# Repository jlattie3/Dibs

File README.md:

## Project Overview

Dibs is a full stack solution for helping students find open study spaces on campus. Light detection sensors send data that updates an iOS application to deliver clear visuals to open spots near them.
Dibs is a Spring 2020 ECE Senior Design project.

## Authors

- Jacob Lattie (iOS)
- Peter Nguyen (Server)
- Dylan Verstandig (BLE)
- Stephen Via (HW Sensor)
- Raish Wadhwaniya (HW Sensor)
- Dr. Lukas Graber (Advisor)

## Gallery

[Demonstration Video](https://www.youtube.com/watch?v=HJM3BfB4vtE)

## Hardware and Software

### Hardware

```
Raspberry Pi 3
nRF52840 Breakout
TLV2462 Op Amp
GL5528 LDR
```

### Software

```
Xcode 11.3.1
iOS 13+
Firebase Console
Adobe XD, Photoshop
```

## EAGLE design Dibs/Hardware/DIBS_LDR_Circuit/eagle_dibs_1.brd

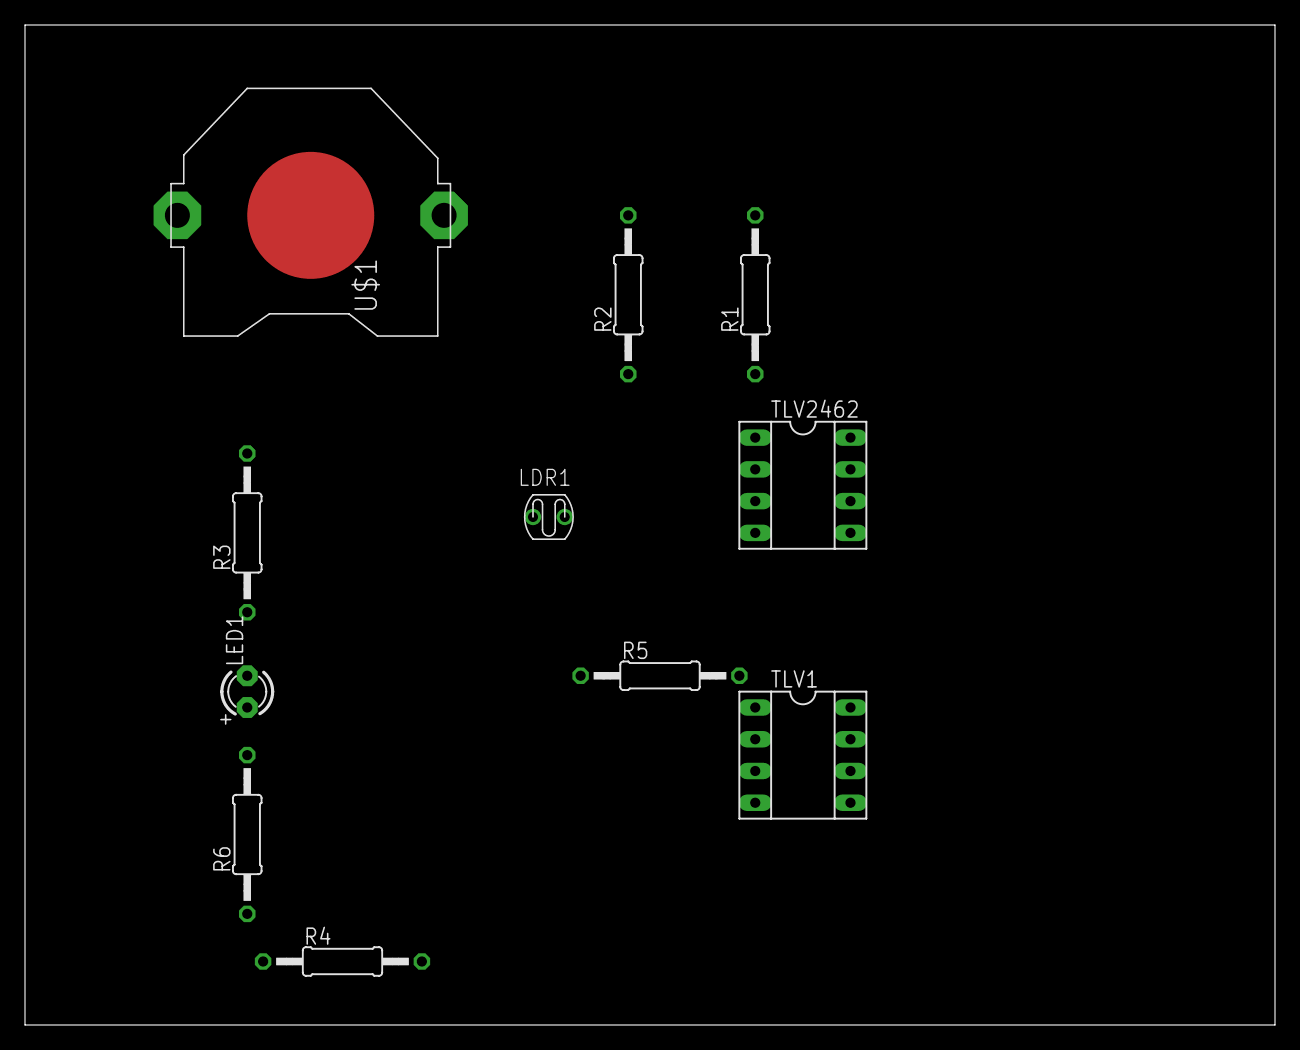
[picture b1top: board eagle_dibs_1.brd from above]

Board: 2 copper layers, 100.0 x 80.0 mm, 11 parts (0 on the bottom side), 8 nets, no tracks yet.

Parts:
LDR1: On: 555 Off: 855; LDR3MM
LED1: LED3MM
R1: 12.5K; 0207/12
R2: 753; 0207/12
R3: 9.166K; 0207/12
R4, R5: 1K; 0207/12
R6: 300; 0207/12
TLV1, TLV2462: Op amps; SOCKET-08
U$1: CR2032; CR2032-THRU

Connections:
GND: LDR1.P$2, LED1.K, R3.1, TLV1.3, TLV1.4, TLV2462.4, U$1.-
unnamed: LDR1.P$1, R1.1, TLV2462.3
unnamed: R2.1, R3.2, TLV2462.2
unnamed: R1.2, R2.2, TLV1.8, TLV2462.8, U$1.+1, U$1.+2
unnamed: LED1.A, R6.2
unnamed: R5.2, R6.1, TLV1.1
unnamed: R4.2, R5.1, TLV1.2
unnamed: R4.1, TLV2462.1

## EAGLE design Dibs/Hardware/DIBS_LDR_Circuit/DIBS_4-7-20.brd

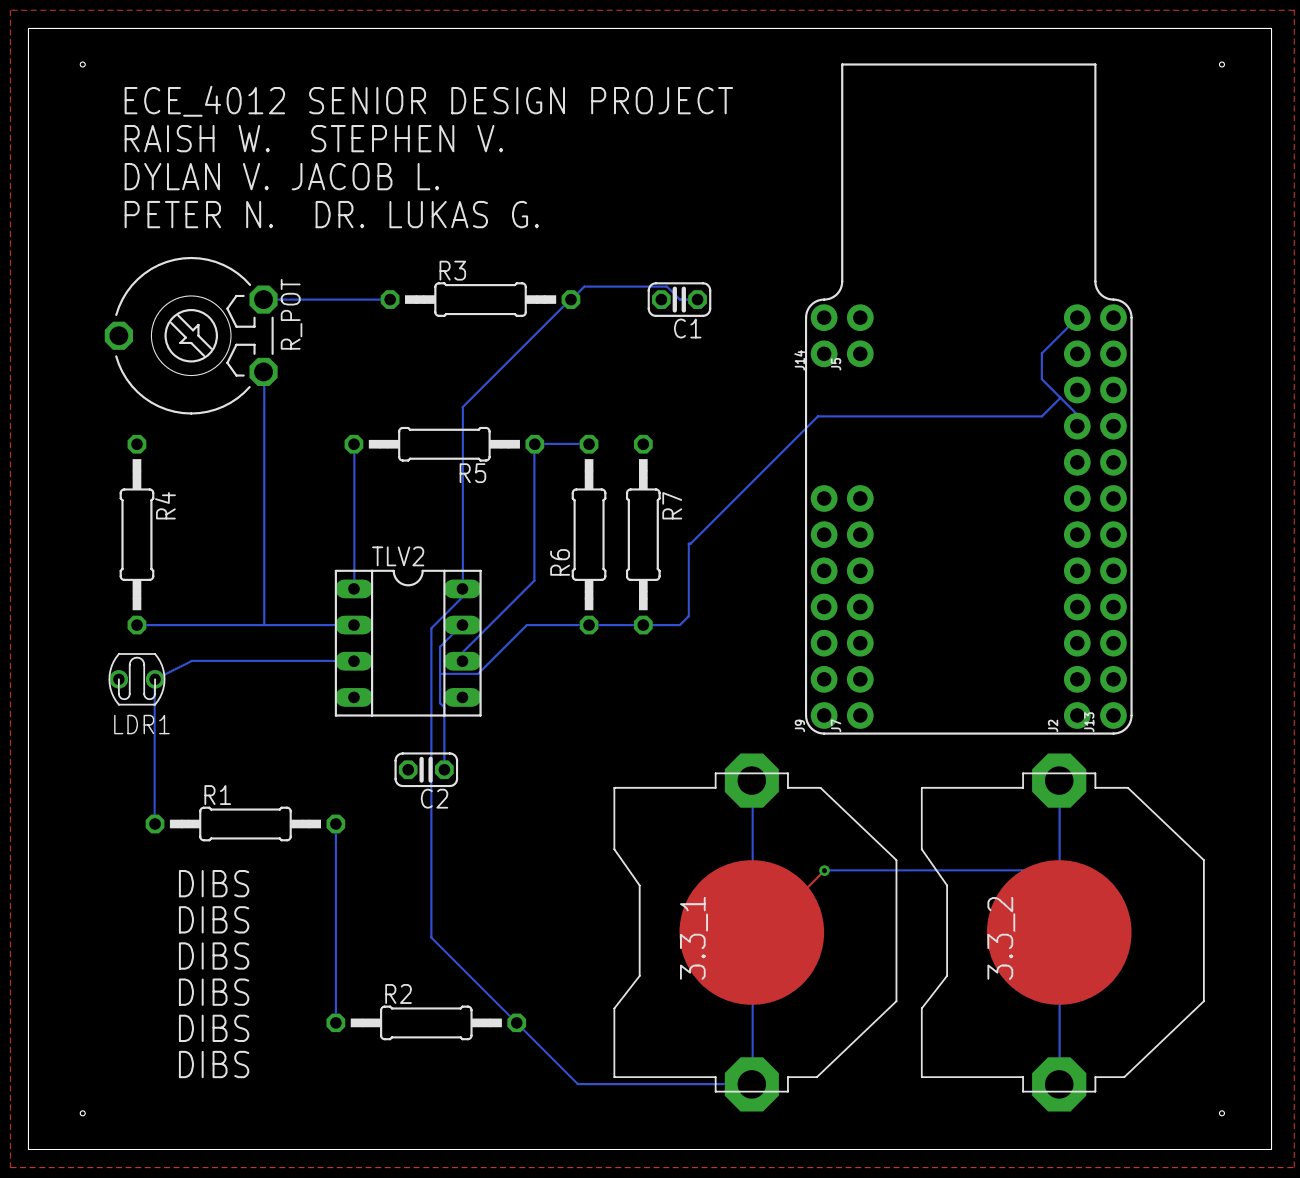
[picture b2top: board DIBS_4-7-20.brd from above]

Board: 2 copper layers, 87.3 x 78.7 mm, 20 parts (0 on the bottom side), 10 nets.

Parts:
3.3_1, 3.3_2: CR2032; CR2032-THRU
C1, C2: 100nF; C025-024X044
J2, J13: 1X12_NO_SILK
J5, J14: 1X02_NO_SILK
J7, J9: 1X07_NO_SILK
LDR1: On: 555 Off: 855; LDR3MM
R1: 1.5K; 0207/12
R2: 11K; 0207/12
R3, R7: 470; 0207/12
R4: 4.7K; 0207/12
R5, R6: 10K; 0207/12
R_POT: 4.7K; LI10
TLV2: Op amps; SOCKET-08

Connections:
GND: 3.3_2.-, C1.2, C2.2, J2.11, J9.1, J9.2, J9.3, J9.4, J9.5, J9.6, J9.7, J13.1, J13.2, J13.3, J13.4, J13.5, J13.6, J13.7, J13.8, J13.9, J13.10, J13.11, J13.12, J14.1, J14.2, LDR1.P$2, R4.1, R7.1, TLV2.4, TLV2.5
unnamed: R5.2, TLV2.1
unnamed: R5.1, R6.2, TLV2.6
unnamed: R3.1, R_POT.E
unnamed: LDR1.P$1, R1.1, TLV2.3
unnamed: 3.3_1.-, 3.3_2.+1, 3.3_2.+2
unnamed: R4.2, R_POT.A, TLV2.2
unnamed: R1.2, R2.1
VCC: 3.3_1.+1, 3.3_1.+2, C1.1, R2.2, R3.2, TLV2.8
VIN: C2.1, J2.9, J2.12, R6.1, R7.2, TLV2.7

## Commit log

2020-01-22 Hardware subdir
2020-01-23 Firebase Database pod
2020-01-23 Database GET from iOS
2020-01-23 Server documentation
2020-01-29 FIR login/persistence
2020-02-10 NFC Testing Support/Entitlements
2020-02-11 Intro view and Scanner view controllers
2020-02-11 Server code updates and Scanner print fix
2020-02-11 Branch test
2020-02-17 Update README.md
    Added installation guide for PyGattLib
2020-02-17 Debug Reformatting
2020-02-21 Login User flow with UI changes
2020-02-26 server code
2020-02-26 AHHH
2020-02-26 Update Firebase child ID
2020-02-26 Move Hardware code
2020-02-27 Safe Firebase read logic
2020-02-27 UI background view and Pod support
2020-03-02 Collection view homepage
2020-03-03 Drag/Drop support for spotCells on homepage
2020-03-03 Custom homepage cell, remove scrollview
2020-03-08 Homepage UI Re-design
2020-03-08 Homepage Cell info
2020-03-09 Homepage UI simplification
2020-03-10 Chair class and full FIR db retrieval
2020-03-10 Click DibsCell to open more info
2020-03-26 File structure
2020-03-30 Fir DB logic inside HomeVC
2020-04-01 Web and iOS DibsSpotVC
2020-04-01 DibsMapView to add new DibsSpot
2020-04-06 CoreData Dibs Cell storage
2020-04-07 Floor Plan view init
2020-04-07 User Default data persistence
2020-04-08 UserDefault persistence and Firebase closure
2020-04-08 Add/Delete logic from MapView
2020-04-14 DibsCell button callbacks and bug fixes
2020-04-17 User account page and basic floor plan
2020-04-18 Final Demo assets and UI
2020-04-21 Add app screen image
2020-04-21 Update README.md
    Add hardware
2020-04-23 Removed Background, updated banner
2020-04-29 PCB files

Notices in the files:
parts and their libraries:
SparkFun-Connectors: Licensing: Creative Commons ShareAlike 4.0 International - https://creativecommons.org/licenses/by-sa/4.0
